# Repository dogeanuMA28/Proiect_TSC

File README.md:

# Proiect_TSC

## BOM(Bill of Materials)
| Componentă | Producator | Cantitate | Link achizitie | Datasheet |
| :--- | :--- | :---: | :--- | :--- |
| **nRF52840** | Nordic Semiconductor | 1 | [Link](https://jlcpcb.com/partdetail/NordicSemicon-NRF52840_QFAA_FR/C3606918) | [Datasheet](https://infocenter.nordicsemi.com/pdf/nRF52840_PS_v1.1.pdf) |
| **BMA423** | Bosch | 1 | [Link](https://jlcpcb.com/partdetail/BoschSensortec-BMA423/C189517) | [Datasheet](https://www.bosch-sensortec.com/media/boschsensortec/downloads/datasheets/bst-bma423-ds004.pdf) |
| **BQ25180YBGR** | Texas Instruments | 1 | [Link](https://jlcpcb.com/partdetail/TexasInstruments-BQ25180YBGR/C3682423) | [Datasheet](https://www.ti.com/lit/ds/symlink/bq25180.pdf) |
| **MAX17048G+T10** | Analog Devices | 1 | [Link](https://jlcpcb.com/partdetail/2777647-MAX17048GT10/C2682616) | [Datasheet](https://datasheets.maximintegrated.com/en/ds/MAX17048-MAX17049.pdf) |
| **DRV2605YZFR** | Texas Instruments | 1 | [Link](https://jlcpcb.com/partdetail/TexasInstruments-DRV2605YZFR/C81079) | [Datasheet](https://www.ti.com/lit/ds/symlink/drv2605.pdf) |
| **RT6160AWSC** | Richtek | 1 | [Link](https://jlcpcb.com/partdetail/RichtekTech-RT6160AWSC/C7065276) | [Datasheet](https://www.richtek.com/assets/product_file/RT6160/DS6160-03.pdf) |
| **2450AT18B100E** | Johanson | 1 | [Link](https://jlcpcb.com/partdetail/JohansonDielectrics-2450AT18B100E/C2917717) | [Datasheet](https://www.johansontechnology.com/datasheets/2450AT18B100E/2450AT18B100E.pdf) |
| **744043680 (L4)** | Wurth | 1 | [Link](https://jlcpcb.com/partdetail/WurthElektronik-744043680/C2045671) | [Datasheet](https://www.we-online.com/catalog/datasheet/744043680.pdf) |
| **FTC252012SR47** | CMT | 1 | [Link](https://jlcpcb.com/partdetail/6763488-FTC252012SR47MBCA/C5832368) | [Datasheet](https://product.tdk.com/en/system/files/dam/doc/product/inductor/inductor/smd/catalog/inductor_commercial_power_ftc252012s_en.pdf) |
| **503480-2400** | Molex | 1 | [Link](https://jlcpcb.com/partdetail/MOLEX-5034802400/C122434) | [Datasheet](https://www.molex.com/pdm_docs/sd/5034802400_sd.pdf) |
| **USB-C 16P** | Kinghelm | 1 | [Link](https://jlcpcb.com/partdetail/Shenzhen_KinghelmElec-KH_TYPE_C16P/C709357) | [Datasheet](https://datasheet.lcsc.com/lcsc/2112151030_Kinghelm-KH-TYPE-C-16P_C2930266.pdf) |
| **EVP-AKE31A** | Panasonic | 3 | [Link](https://jlcpcb.com/partdetail/PANASONIC-EVPAKE31A/C569760) | [Datasheet](https://industrial.panasonic.com/ww/products/pt/tactile-sw/models/EVPAKE31A) |
| **USBLC6-2SC6Y** | STMicroelectronics | 1 | [Link](https://jlcpcb.com/partdetail/STMicroelectronics-USBLC62SC6Y/C2969755) | [Datasheet](https://www.st.com/resource/en/datasheet/usblc6-2.pdf) |
| **MBR0530** | JCET | 3 | [Link](https://jlcpcb.com/partdetail/78464-MBR0530/C77336) | [Datasheet](https://www.onsemi.com/pdf/datasheet/mbr0530t1-d.pdf) |
| **SI1308EDL** | Vishay | 1 | [Link](https://jlcpcb.com/partdetail/VishayIntertech-SI1308EDL_T1GE3/C469327) | [Datasheet](https://www.vishay.com/docs/72013/si1308edl.pdf) |
| **DMG2305UX-7** | TECH PUBLIC | 1 | [Link](https://jlcpcb.com/partdetail/TECHPUBLIC-DMG2305UX/C2940629) | [Datasheet](https://www.diodes.com/assets/Datasheets/DMG2305UX.pdf) |
| **GRM0335C1E101JA01D** | Murata Electronics | 10 | [Link](https://jlcpcb.com/partdetail/MurataElectronics-GRM0335C1E101JA01D/C76917) | [Datasheet](https://docs.rs-online.com/3c16/A700000008615521.pdf) |
| **Condensatoare(0402)** | Samsung Electro-Mechanics | 21 | [Link](https://jlcpcb.com/partdetail/Samsung_Electro_Mechanics-CL05A105KB5NQNC/C52923) | [Datasheet](https://www1.futureelectronics.com/doc/Samsung%20Electro-Mechanics/CL05A105KA5NQNC-SMP.pdf) |
| **Condensatoare(0201)** | Samsung Electro-Mechanics | 17 | [Link](https://jlcpcb.com/partdetail/Murata_Electronics-GRM033R61A104KE84D/C1619) | [Datasheet](https://docs.rs-online.com/3c16/A700000008615521.pdf) |
| **Rezistente(0201)** | UNI-ROYAL | 17 | [Link](https://jlcpcb.com/parts/componentSearch?searchTxt=0201%20resistor) | [Datasheet](https://jlcpcb.com/api/file/downloadByFileSystemAccessId/8590910972175327232) |

## Functionalitati hardware

### LiPo Charger
Circuitul incarca o baterie LiPo (Lithium-Polymer), controland tensiunea si curentul pentru a preveni supraincarcarea, deteriorarea sau riscul de incendiu. Comunica folosind I2C cu nRF52840.

### Fuel Gauge
Circuitul masoara nivelului bateriei. El alerteaza ceasul cand nivelul bateriei este scazut. Comunica folosind I2C cu nRF52840.

### DC/DC
Circuitul alimenteaza si transforma tensiunea in alte tensiuni stabile, necesare pentru alte componente ale ceasului. Comunica folosind 
I2C cu nRF52840.

### E-Paper Connector
Circuitul este conexiunea la ecranul E-Paper. Comunica folosind SPI cu nRF52840.

### E-Paper Drive Circuit
Circuit de comanda care genereaza si controleaza tensiunile si semnalele necesare pentru a actualiza un afisaj E-Paper. Gestioneaza
procesul de schimbare al pixelilor pentru a afisaj.

### USB-C Connector
Circuitul reprezintă mufa USB. Asigura alimentare, transfer de date si semnal video între dispozitive.

### ESD Protection
Circuitul protejează electronica sensibila din USB impotriva descarcarilor electrostatice bruste, limitand tensiunile mari și devierea
curentului către masa pentru a preveni deteriorarea componentelor.

### SWD
Circuitul este folosit pentru debugging. Poate fi conectat la JTAG.

### Haptic Driver
Circuitul genereaza vibratii, transformand semnale digitale din microcontroler in impulsuri precise de vibratie. Comunica folosind I2C cu 
nRF52840.

### IMU
Circuitul masoara acceleratia si directia ceasului. Comunica folosind I2C cu nRF52840.

## nRF52840 - descrierea pinilor
* **P$AD12 (EPD_BUSY)** - conexiune care arata daca ecranul este ocupat (E-Paper Display)
* **P$AD10 (EPD_DC)** - conexiune data/command(E-Paper Display)
* **P$K2 (EPD_CS)** - conexiune chip select(E-Paper Display)
* **P$AD12 (EPD_RST)** - conexiune pentru resetare(E-Paper Display)
* **P$A12 (SCK)** - clock SPI(E-Paper Display)
* **P$P13 (MOSI)** - data(master out slave in) SPI(E-Paper Display).
* **P$Y23 (P1.01)** - conexiune circuit de comanda
* **P$AD8 (P0.13)** - buton din stanga
* **P$AC9 (P0.14)** - buton din mijloc
* **P$W24 (P1.02)** - buton din dreapta
* **P$AD6 (D+)** - traseu diferențial pozitiv pentru ESD Protection
* **P$AD4 (D-)** - traseu diferențial negativ pentru ESD Protection.
* **P$AD2 (VBUS)** - conexiune VBUS(USB)
* **P$U1 (HAPTIC_EN)** - conexiune enable/disable(Haptic Driver)
* **P$T2 (PMIC_INT)** - intrerupere(LiPo Battery)
* **P$P2 (IMU_INT2)** - intrerupere(IMU)
* **P$N1 (IMU_INT1)** - intrerupere(IMU)
* **P$M2 (SCL)** - clock I2C
* **P$L1 (SDA)** - data I2C
* **P$J24 (ALERT)** - conexiune cu alerta(Fuel Gauge)
* **P$AD22 (SWO)** - conexiune pentru debug(TP_SWO)
* **P$AC13 (RESET)** - conexiune pentru resetarea componentei(TP_RESET, SWD)
* **P$AA24 (SWDCLK)** - conexiune pentru debug(SWD)
* **P$AC24 (SWDIO)** - conexiune input/output(SWD)
* **P$F2 și P$D2** - ceasul de 32 kHz
* **P$A23 și P$A24** - ceasul de 32 MHz
* **P$H23, P$F23** - conexiune antena antenă.

## Rutare

Cablajul imprimat (PCB) este realizat pe **4 straturi (4-layer stack-up)**:
* **Top** – rutarea semnalelor si plasarea componentelor
* **GND** – plan de masa continuu (GND)
* **Power** – plan de alimentare
* **Bottom** – rutarea semnalelor

**DC/DC**, **LiPo Charger** si **Fuel Gauge** le-am pozitionat apropiate pentru a oferi un transfer transfer de putere cat mai eficient.
**E-Paper Drive Circuit** a fost izolat in partea de stanga sus(dar tot aproape de **E-Paper Display Connector**) pentru a evita zgomotele
care ar putea fi produse de bobina si care ar putea afecta semnalel SPI, busy sau reset din **E-Paper Display Connector**.
**Haptic Driver** este tinut la distanta de IMU pentru a preveni interferentele din cauza vibratiilor.

## Erori

### via-smd
Am acceptat erorile astea pentru a majoritatea provin din faptul ca am facut vi-in-pad pentru GND.

### smd-via
Le-am acceptat pentru ca fie vin din acelasi motiv ca erorile de mai sus fie de la nRF52840 pentru ca a trebuit
sa pun via-in-pad pentru a conecta cu intrarile de mai din interior.

### solid-poligon-shape
Sunt erori de la butoane. Cred ca este de la disignul lor si nu le pot rezolva.

### via-via
Acestea provin tot de la nRF52840, tot pe intrarile de mai din interior. Le-am acceptat pentru ca altfel nu puteam
conecta firele pentru ca spatiul era mult prea mic.

### via, drill size
Tot ca mai sus. Am fost nevoit sa folosesc via pentru a conecta firele. Spatiul fiid prea mic a trabuit sa
folosesc drill size mai mic de 0.3mm cum precizeaza rule-urile.

### smd-hole
Problema vine de la USB. Tot designul este prblema. Nu am stiut cum sa rezolv aceasta problema fara sa modific
efectiv designul componentei.

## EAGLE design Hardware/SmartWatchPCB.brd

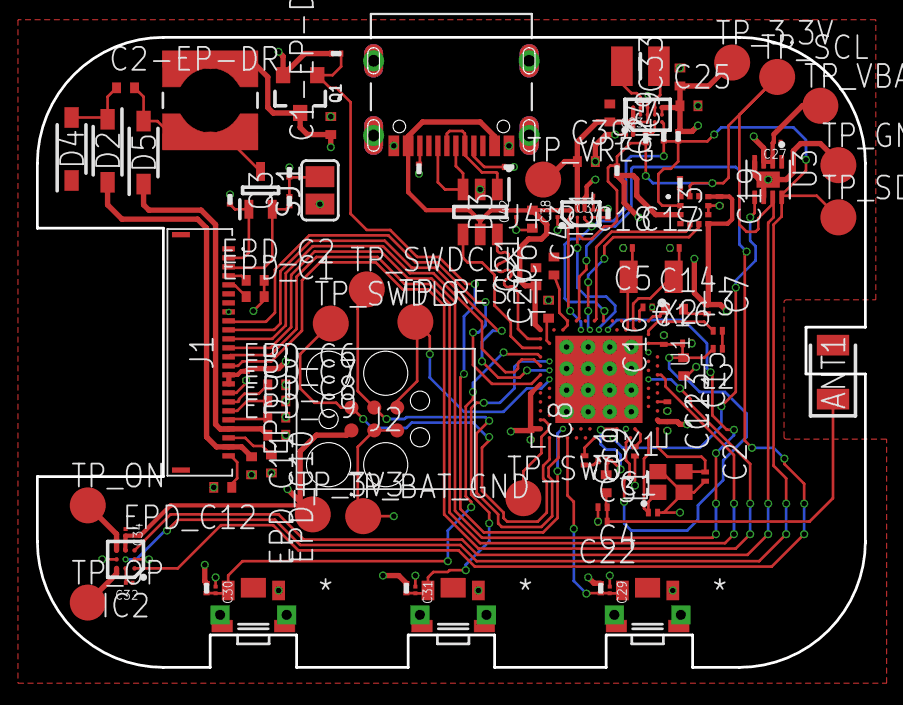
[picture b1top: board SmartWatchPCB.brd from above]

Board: 4 copper layers, 46.0 x 35.0 mm, 105 parts (0 on the bottom side), 73 nets.

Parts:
ANT1: 2450AT18B100E; 2450AT18B100E_ANTC3216X140N
C1, C2, C17, C18: 12pF; NORDIC_NRF_3_RESC0201_L
C1-EP-DR, C24, C39: 10uF; NORDIC_NRF_3_RESC0402_L
C2-EP-DR: 4.7uF/25V; NORDIC_NRF_3_RESC0402_L
C3, C4: 1pF; NORDIC_NRF_3_RESC0201_L
C5, C7, C8, C12, C19: 100nF; NORDIC_NRF_3_RESC0201_L
C6, C14, C20, C21, C43: 4.7uF; NORDIC_NRF_3_RESC0402_L
C9: 820pF; NORDIC_NRF_3_RESC0201_L
C10, C13, C22: N.C.; NORDIC_NRF_3_RESC0201_L
C11: 100pF; NORDIC_NRF_3_RESC0201_L
C15: 1.0uF; NORDIC_NRF_3_RESC0402_L
C16: 47nF; NORDIC_NRF_3_RESC0201_L
C23, C27, C34, C42: 0.1uF; GRM011R60J152KE01L_2_CAPC0201X13N
C25, C33: 22uF; NORDIC_NRF_3_RESC0402_L
C29, C30, C31, C32, C37, C38: 1uF; GRM011R60J152KE01L_2_CAPC0201X13N
D2, D4, D5: MBR0530; ESP32_C6_LIBRARY_5_SOD3716X135N
D3: USBLC6-2SC6Y; ESP32_C6_LIBRARY_3_SOT95P280X145-6N
EPD_C1, EPD_C2, EPD_C6, EPD_C7, EPD_C8, EPD_C9, EPD_C10, EPD_C11, EPD_C12: 1uF/50V; NORDIC_NRF_3_RESC0402_L
EPD_C5: 0.1uF/50V; NORDIC_NRF_3_RESC0201_L
IC1: BQ25180YBGR; BQ25180YBGR_BGA8C40P2X4_100X155X50
IC2: DRV2605YZFR; DRV2605YZFR_BGA9C50P3X3_144X144X62
IC3: BMA423_BMA423
IC9: RT6160AWSC; RT6160AWSC_BGA15C40P3X5_140X230X60
J1: 503480-2400; 503480-2400_5034802400
J2: TC2030-IDC; TC2030-IDC_TC2030IDC
J4: KH-TYPE-C-16P; KH-TYPE-C-16P_KINGHELM_KH-TYPE-C-16P
L1: 3.9nH; NORDIC_NRF_2_RESC0402_L
L2: 10uH; NORDIC_NRF_2_RESC0201_L
L3: 15nH; NORDIC_NRF_2_RESC0201_L
L5: 48uH; ESP32_C6_LIBRARY_2_IND_4828-WE-TPC_WRE
L7: FTC252012SR47MBCA; MLP2016SR47MT0S1_INDC2016X100N
Q1: 20V/4.2A/52mΩ/1.4W; ESP32_C6_LIBRARY_4_ESP32_C6_LIBRARY_4_ESP32_C6_LIBRARY_4_ES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
Q3: SI1308EDL-T1-GE3; ESP32_C6_LIBRARY_6_SOT65P210X110-3N
R1_EP_DR: 0.47; CPF0201D7K68C1_0201
R1_USB, R2_USB: 5K1; CPF0201D7K68C1_0201
R2, R3, R4: 0; CPF0201D7K68C1_0201
R2_EP_DR, R5, R7, R8: 10k; CPF0201D7K68C1_0201
R9: 10K; CPF0201D7K68C1_0201
R17: 3k3; CPF0201D7K68C1_0201
R18: 3K3; CPF0201D7K68C1_0201
R_PWR_EPD: 10k; CPF0201D7K68C1_0201
R_TYPE_SEL: 2.2; CPF0201D7K68C1_0201
SJ1: ESP32_C6_LIBRARY_7_JUMPER_SJ
SW_DN: EVP-AKE31A_PAN; 2025-10-22_07-23-44_LIBRARY_SW_EVP-AKE31A_PAN
SW_ENT: EVP-AKE31A_PAN; 2025-10-22_07-23-44_LIBRARY_SW_EVP-AKE31A_PAN
SW_UP: EVP-AKE31A_PAN; 2025-10-22_07-23-44_LIBRARY_SW_EVP-AKE31A_PAN
TP_3.3V, TP_3V3: HECTOR_WATCH_1_TPTP20R; HECTOR_WATCH_1_TP20R
TP_BAT_GND: HECTOR_WATCH_1_TPTP20R; HECTOR_WATCH_1_TP20R
TP_GND: HECTOR_WATCH_1_TPTP20R; HECTOR_WATCH_1_TP20R
TP_ON: HECTOR_WATCH_1_TPTP20R; HECTOR_WATCH_1_TP20R
TP_OP: HECTOR_WATCH_1_TPTP20R; HECTOR_WATCH_1_TP20R
TP_RESET: HECTOR_WATCH_1_TPTP20R; HECTOR_WATCH_1_TP20R
TP_SCL: HECTOR_WATCH_1_TPTP20R; HECTOR_WATCH_1_TP20R
TP_SDA: HECTOR_WATCH_1_TPTP20R; HECTOR_WATCH_1_TP20R
TP_SWDCLK: HECTOR_WATCH_1_TPTP20R; HECTOR_WATCH_1_TP20R
TP_SWDIO: HECTOR_WATCH_1_TPTP20R; HECTOR_WATCH_1_TP20R
TP_SWO: HECTOR_WATCH_1_TPTP20R; HECTOR_WATCH_1_TP20R
TP_VBAT: HECTOR_WATCH_1_TPTP20R; HECTOR_WATCH_1_TP20R
TP_VREG: HECTOR_WATCH_1_TPTP20R; HECTOR_WATCH_1_TP20R
U1: NRF52840_QF; NORDIC_NRF_4_AQFN50P700X700X85_HS-74N
U3: MAX17048G+T10; ESP32_C6_LIBRARY_SON50P200X200X80-9N
X1: 32MHz; NORDIC_NRF_BT-XTAL_2016_N
X2: 32.768kHz; NORDIC_NRF_1_XTAL_3215_N

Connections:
3V3: C7.1, C8.1, C12.1, C19.1, C25.1, C33.1, C34.2, IC2.C2, IC3.3, IC3.7, IC3.10, IC9.E2, IC9.E3, J2.1, Q1.2, R5.2, R7.2, R8.2, R17.1, R18.1, R_PWR_EPD.2, TP_3.3V.TP, TP_3V3.TP, U1.P$A22, U1.P$AD14, U1.P$AD23
ALERT: U1.P$J24, U3.5
D+: D3.4, U1.P$AD6
D-: D3.6, U1.P$AD4
DEC1: C5.1, U1.P$C1
DN: D3.1, J4.A7, J4.B7
DP: D3.3, J4.A6, J4.B6
EPD_3V3: C1-EP-DR.1, EPD_C5.1, J1.15, J1.16, L5.2, Q1.3
EPD_BUSY: J1.9, U1.P$AD12
EPD_CS: J1.12, U1.P$K2
EPD_DC: J1.11, U1.P$AD10
EPD_RST: J1.10, U1.P$AC11
GDR: J1.2, Q3.1, R2_EP_DR.2
GND: C1.2, C1-EP-DR.2, C2.2, C3.2, C4.2, C5.2, C6.2, C8.2, C9.2, C10.2, C11.1, C12.2, C13.2, C15.2, C16.2, C17.1, C18.1, C19.2, C20.2, C21.2, C22.2, C23.1, C24.1, C25.2, C27.1, C29.1, C30.1, C31.1, C32.1, C33.2, C34.1, C37.1, C38.1, C39.2, C42.1, C43.2, D3.2, D4.1, EPD_C1.2, EPD_C2.2, EPD_C5.2, EPD_C6.2, EPD_C7.2, EPD_C8.2, EPD_C9.2, EPD_C10.2, EPD_C11.2, EPD_C12.2, IC1.D2, IC2.B1, IC2.B3, IC3.8, IC3.9, IC9.B1, IC9.C1, IC9.C2, IC9.C3, J1.8, J1.17, J1.MP1, J1.MP2, J2.3, J2.5, J4.A1_B12, J4.A12_B1, J4.SH1, J4.SH2, J4.SH3, J4.SH4, R1_USB.1, R2_EP_DR.1, R2_USB.2, R3.1, R9.1, R_TYPE_SEL.1, SJ1.1, SW_DN.1, SW_ENT.1, SW_UP.1, TP_BAT_GND.TP, TP_GND.TP, U1.P$74, U1.P$75, U1.P$76, U1.P$77, U1.P$78, U1.P$79, U1.P$80, U1.P$81, U1.P$82, U1.P$83, U1.P$84, U1.P$85, U1.P$86, U1.P$87, U1.P$88, U1.P$89, U1.P$90, U1.P$B7, U1.P$F23, U3.1, U3.4, U3.6, U3.9, X1.2, X1.4
HAPTIC_EN: IC2.A1, U1.P$U1
IMU_INT1: IC3.5, U1.P$N1
IMU_INT2: IC3.6, U1.P$P2
LX1: IC9.B2, IC9.B3, L7.1
LX2: IC9.D2, IC9.D3, L7.2
MOSI: J1.14, U1.P$B13
unnamed: IC1.D1, R9.2
unnamed: IC9.D1, R4.2
unnamed: IC9.E1, R2.2
unnamed: IC3.1, R3.2
unnamed: C20.1, U1.P$AC5
unnamed: C17.2, U1.P$D2, X2.1
unnamed: C18.2, U1.P$F2, X2.2
unnamed: C6.1, U1.P$W1, U1.P$Y2
unnamed: C7.2, C14.2
unnamed: C14.1, U1.P$B1
unnamed: L2.1, U1.P$B3
unnamed: L2.2, L3.1
unnamed: C10.1, C15.1, C16.1, L3.2, U1.P$B5, U1.P$E24
unnamed: C1.1, U1.P$B24, X1.1
unnamed: C2.1, U1.P$A23, X1.3
unnamed: C11.2, U1.P$D23
unnamed: C3.1, L1.1, U1.P$H23
unnamed: ANT1.1, C4.1, C22.1, L1.2
unnamed: C9.1, U1.P$N24
unnamed: C2-EP-DR.2, D5.2, L5.1, Q3.3
unnamed: C2-EP-DR.1, D2.1, D4.2
unnamed: EPD_C1.1, J1.5
unnamed: C13.1, U1.P$A18
unnamed: R1_EP_DR.1, R_TYPE_SEL.2, SJ1.2
unnamed: EPD_C2.1, J1.4
unnamed: C32.2, IC2.A2
unnamed: J4.B5, R2_USB.1
unnamed: J4.A5, R1_USB.2
unnamed: EPD_C6.1, J1.18
unnamed: EPD_C7.1, J1.19
unnamed: EPD_C8.1, J1.20
unnamed: EPD_C10.1, J1.22
unnamed: EPD_C12.1, J1.24
OUT+: IC2.A3, TP_OP.TP
OUT-: IC2.C3, TP_ON.TP
P0.13: C30.2, R5.1, SW_UP.2, U1.P$AD8
P0.14: C31.2, R8.1, SW_ENT.2, U1.P$AC9
P1.01: Q1.1, R_PWR_EPD.1, U1.P$Y23
P1.02: C29.2, R7.1, SW_DN.2, U1.P$W24
PMIC_INT: IC1.A1, U1.P$T2
PREVGH: D5.1, EPD_C9.1, J1.21
PREVGL: D2.2, EPD_C11.1, J1.23
RESE: J1.3, Q3.2, R1_EP_DR.2
RESET: J2.6, TP_RESET.TP, U1.P$AC13
SCK: J1.13, U1.P$A12
SCL: IC1.B1, IC2.C1, IC3.12, R4.1, R17.2, TP_SCL.TP, U1.P$M2, U3.7
SDA: IC1.C1, IC2.B2, IC3.2, R2.1, R18.2, TP_SDA.TP, U1.P$L1, U3.8
SWDCLK: J2.4, TP_SWDCLK.TP, U1.P$AA24
SWDIO: J2.2, TP_SWDIO.TP, U1.P$AC24
SWO: TP_SWO.TP, U1.P$AD22
VBAT: C27.2, C37.2, IC1.C2, TP_VBAT.TP, U3.2, U3.3
VBUS: C21.1, C38.2, C42.2, C43.1, D3.5, IC1.A2, J4.A4_B9, J4.A9_B4, U1.P$AD2
VREG: C23.2, C24.2, C39.1, IC1.B2, IC9.A1, IC9.A2, IC9.A3, TP_VREG.TP

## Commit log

2026-04-10 first
2026-04-22 blyat
2026-04-22 Actualizare README

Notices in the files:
parts and their libraries:
COPYRIGHT: Copyright (C) 2025 Ultra Librarian. All rights reserved.
COPYRIGHT: Copyright (C) 2024 Ultra Librarian. All rights reserved.
